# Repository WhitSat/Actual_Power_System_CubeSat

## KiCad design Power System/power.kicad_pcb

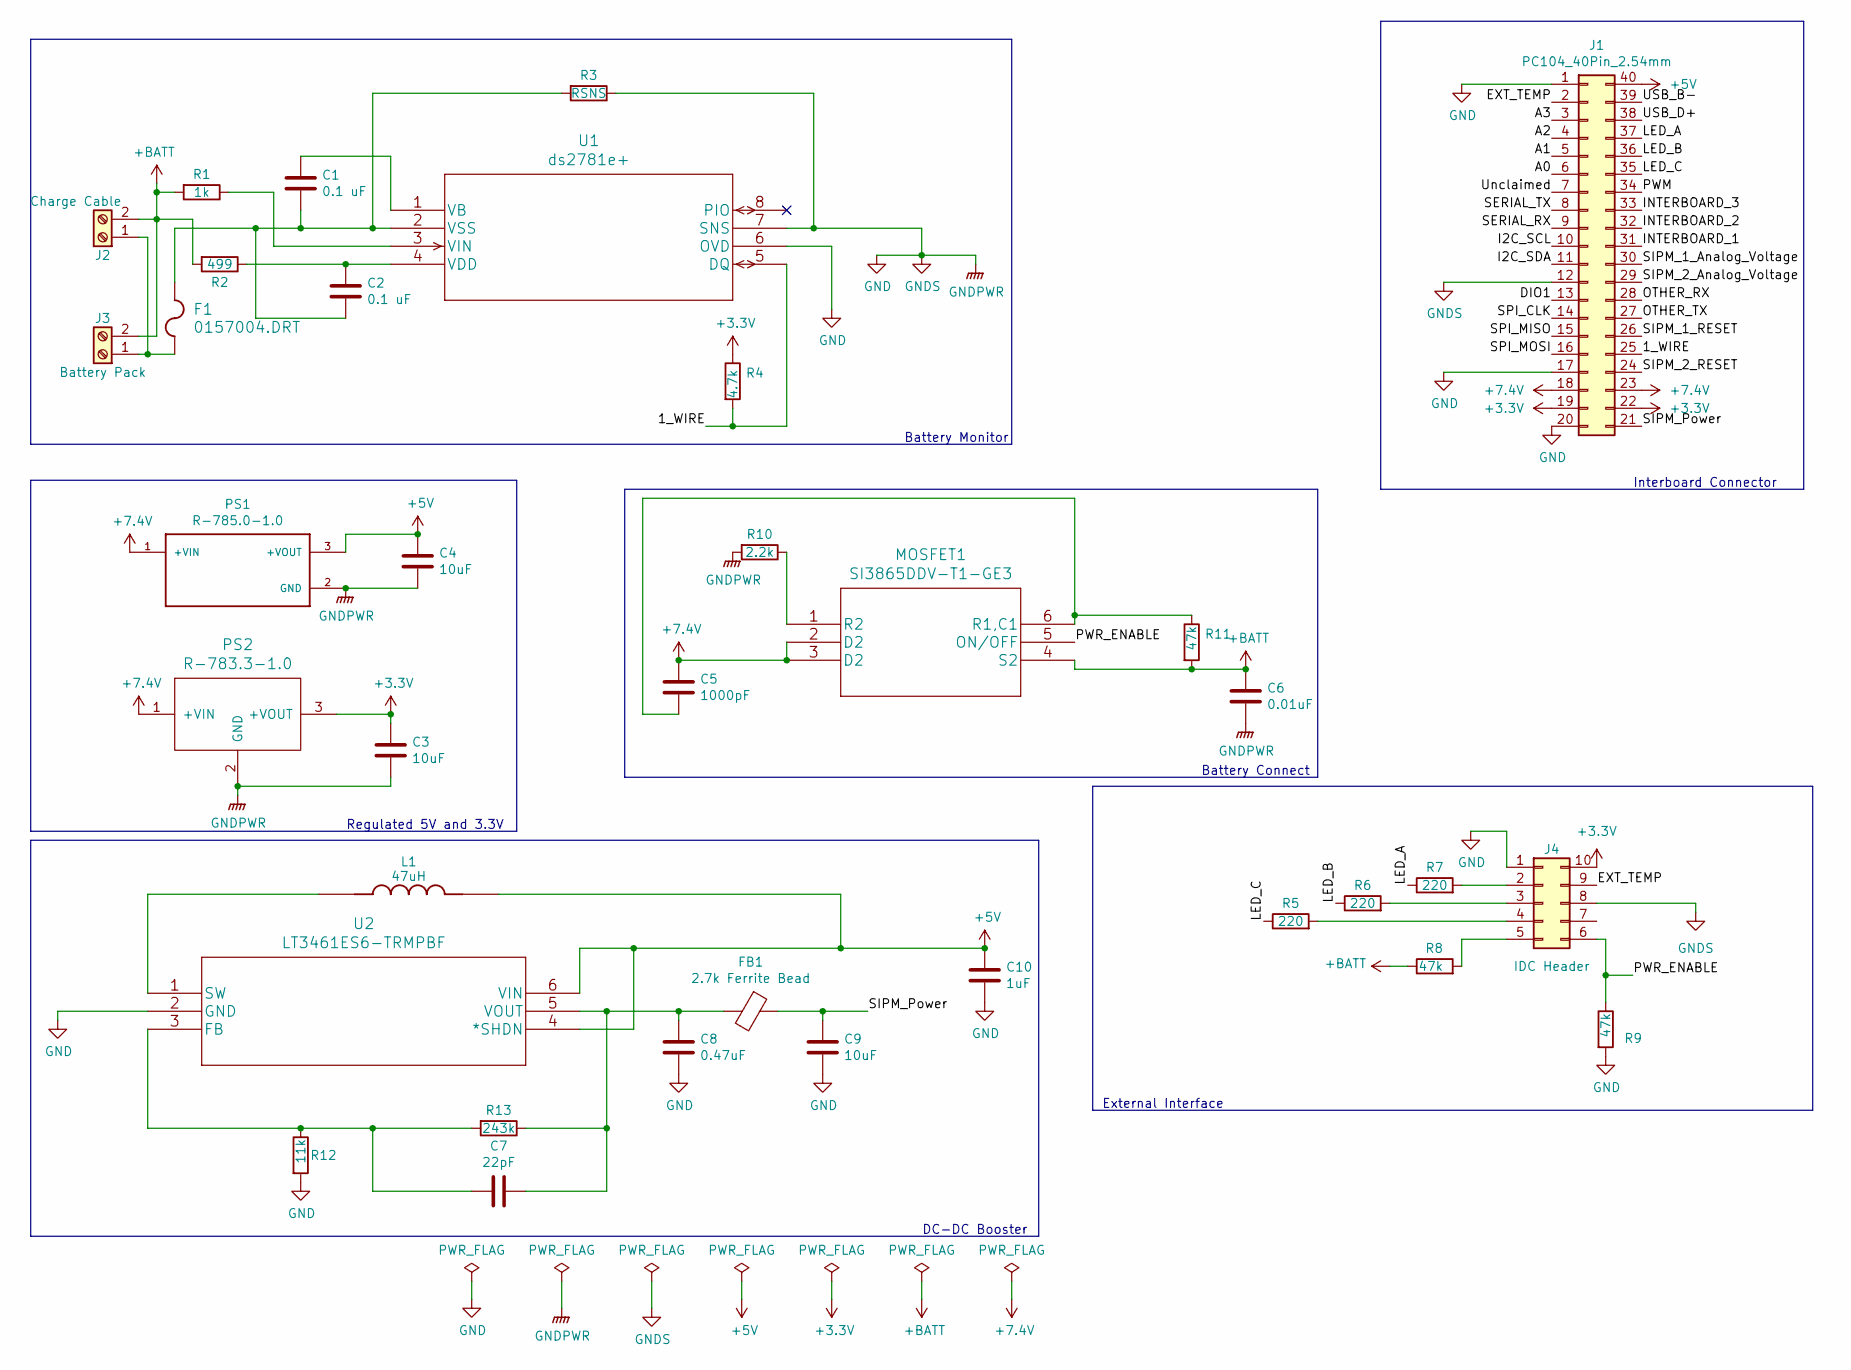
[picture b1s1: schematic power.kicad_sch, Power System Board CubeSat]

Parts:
C1, C2: 0.1 uF; C_1206_3216Metric_Pad1.33x1.80mm_HandSolder
C3, C4, C9: 10uF; C_1206_3216Metric_Pad1.33x1.80mm_HandSolder
C5: 1000pF; C_1206_3216Metric_Pad1.33x1.80mm_HandSolder
C6: 0.01uF; C_1206_3216Metric_Pad1.33x1.80mm_HandSolder
C7: 22pF; C_1206_3216Metric_Pad1.33x1.80mm_HandSolder
C8: 0.47uF; C_1206_3216Metric_Pad1.33x1.80mm_HandSolder
C10: 1uF; C_1206_3216Metric_Pad1.33x1.80mm_HandSolder
F1: 0157004.DRT; LittleFuse_0157004.DRT
FB1: 2.7k Ferrite Bead; BEADC2012X110N
J1: PC104_40Pin_2.54mm; PC104_40PinSocket_2.54mm
J2: Charge Cable; TerminalBlock_4Ucon_1x02_P3.50mm_Horizontal
J3: Battery Pack; TerminalBlock_4Ucon_1x02_P3.50mm_Horizontal
J4: IDC Header; IDC-Header_2x05_P2.54mm_Vertical
L1: 47uH; IND_LQH43NH470J03L; PARTREV N/A
MOSFET1: SI3865DDV-T1-GE3
PS1: R-785.0-1.0; RECOM-R-78xx-1.0
PS2: R-783.3-1.0; RECOM-R-78xx-1.0
R1: 1k; R_1206_3216Metric_Pad1.30x1.75mm_HandSolder
R2: 499; R_1206_3216Metric_Pad1.30x1.75mm_HandSolder
R3: RSNS; R_2010_5025Metric_Pad1.40x2.65mm_HandSolder
R4: 4.7k; R_1206_3216Metric_Pad1.30x1.75mm_HandSolder
R5, R6, R7: 220; R_1206_3216Metric_Pad1.30x1.75mm_HandSolder
R8, R9, R11: 47k; R_1206_3216Metric_Pad1.30x1.75mm_HandSolder
R10: 2.2k; R_1206_3216Metric_Pad1.30x1.75mm_HandSolder
R12: 11k; R_1206_3216Metric_Pad1.30x1.75mm_HandSolder
R13: 243k; R_1206_3216Metric_Pad1.30x1.75mm_HandSolder
U1: ds2781e+; ds2781e&plus_
U2: LT3461ES6-TRMPBF

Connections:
+3V3: C3.1, J1.19, J1.22, J4.10, PS2.3 (+VOUT), R4.1
+5V: C4.1, C10.1, J1.40, L1.2, PS1.3 (+VOUT), U2.4 (*SHDN), U2.6 (VIN)
+7.4V: C5.1, J1.18, J1.23, MOSFET1.2 (D2), MOSFET1.3 (D2), PS1.1 (+VIN), PS2.1 (+VIN)
+BATT: C6.1, J2.2, J3.2, MOSFET1.4 (S2), R1.2, R2.2, R8.1, R11.2
/1_WIRE: J1.25, R4.2, U1.5 (DQ)
/A0: J1.6
/A1: J1.5
/A2: J1.4
/A3: J1.3
/DIO1: J1.13
/EXT_TEMP: J1.2, J4.9
/I2C_SCL: J1.10
/I2C_SDA: J1.11
/INTERBOARD_1: J1.31
/INTERBOARD_2: J1.32
/INTERBOARD_3: J1.33
/LED_A: J1.37, R7.1
/LED_B: J1.36, R6.1
/LED_C: J1.35, R5.1
/OTHER_RX: J1.28
/OTHER_TX: J1.27
/PWM: J1.34
/PWR_ENABLE: J4.6, MOSFET1.5 (ON/OFF), R9.1
/SERIAL_RX: J1.9
/SERIAL_TX: J1.8
/SIPM_1_Analog_Voltage: J1.30
/SIPM_1_RESET: J1.26
/SIPM_2_Analog_Voltage: J1.29
/SIPM_2_RESET: J1.24
/SIPM_Power: C9.1, FB1.1, J1.21
/SPI_CLK: J1.14
/SPI_MISO: J1.15
/SPI_MOSI: J1.16
/USB_B-: J1.39
/USB_D+: J1.38
/Unclaimed: J1.7
GND: C3.2, C4.2, C6.2, C8.2, C9.2, C10.2, J1.1, J1.12, J1.17, J1.20, J4.1, J4.8, PS1.2 (GND), PS2.2 (GND), R3.1, R9.2, R10.2, R12.2, U1.6 (OVD), U1.7 (SNS), U2.2 (GND)
unnamed: C1.1, U1.1 (VB)
unnamed: C1.2, C2.2, F1.2, R3.2, U1.2 (VSS)
unnamed: C2.1, R2.1, U1.4 (VDD)
unnamed: C5.2, MOSFET1.6 (R1,C1), R11.1
unnamed: C7.1, C8.1, FB1.2, R13.1, U2.5 (VOUT)
unnamed: C7.2, R12.1, R13.2, U2.3 (FB)
unnamed: F1.1, J2.1, J3.1
unnamed: L1.1, U2.1 (SW)
unnamed: MOSFET1.1 (R2), R10.1
unnamed: R1.1, U1.3 (VIN)
unnamed: J4.4, R5.2
unnamed: J4.3, R6.2
unnamed: J4.2, R7.2
unnamed: J4.5, R8.2

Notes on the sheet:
Interboard Connector
Battery Monitor
External Interface
DC-DC Booster
Regulated 5V and 3.3V
Battery Connect

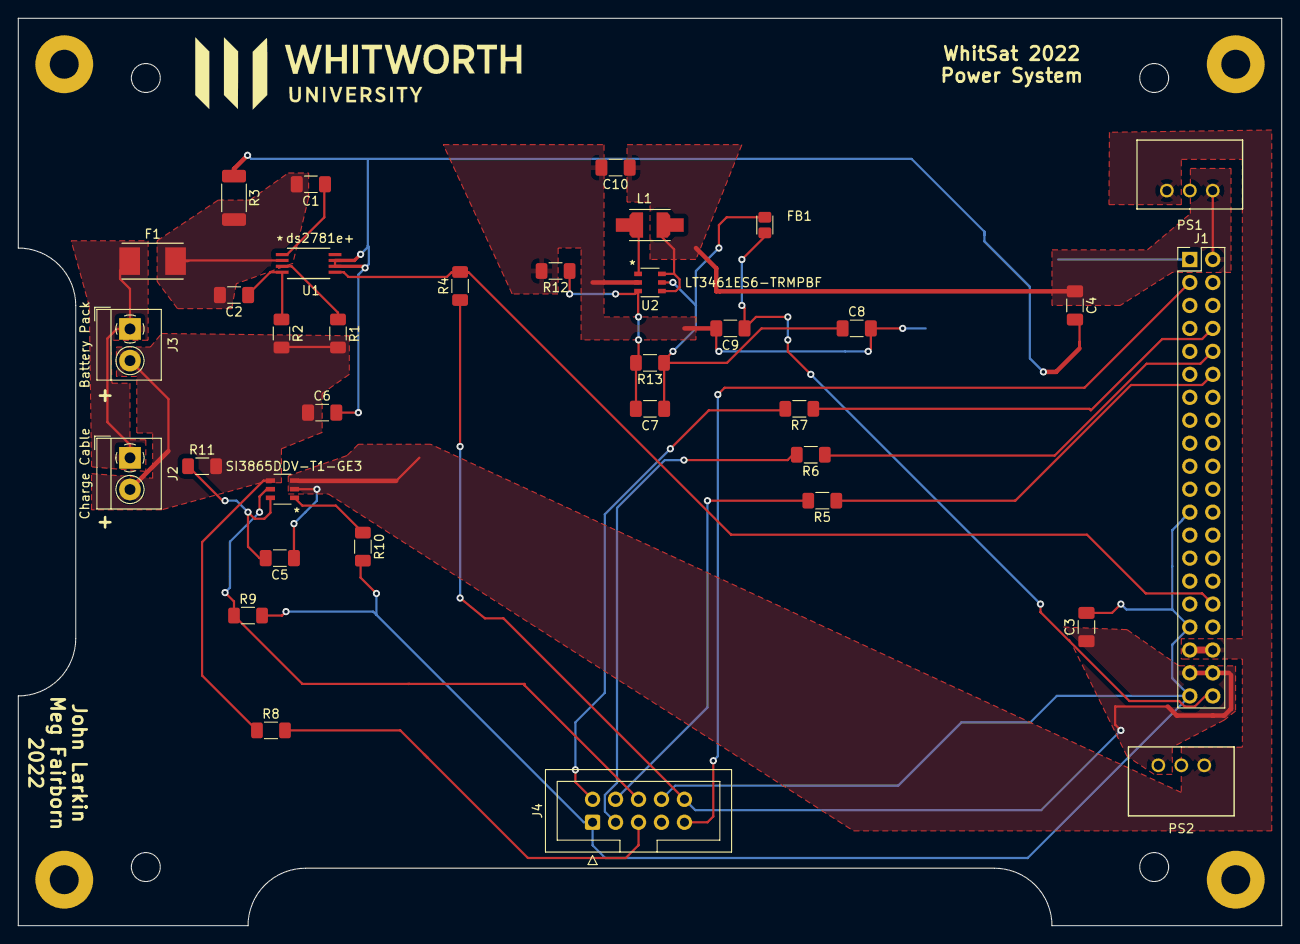
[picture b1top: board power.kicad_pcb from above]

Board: 2 copper layers, 139.7 x 100.3 mm, 35 parts (0 on the bottom side), 26 nets.

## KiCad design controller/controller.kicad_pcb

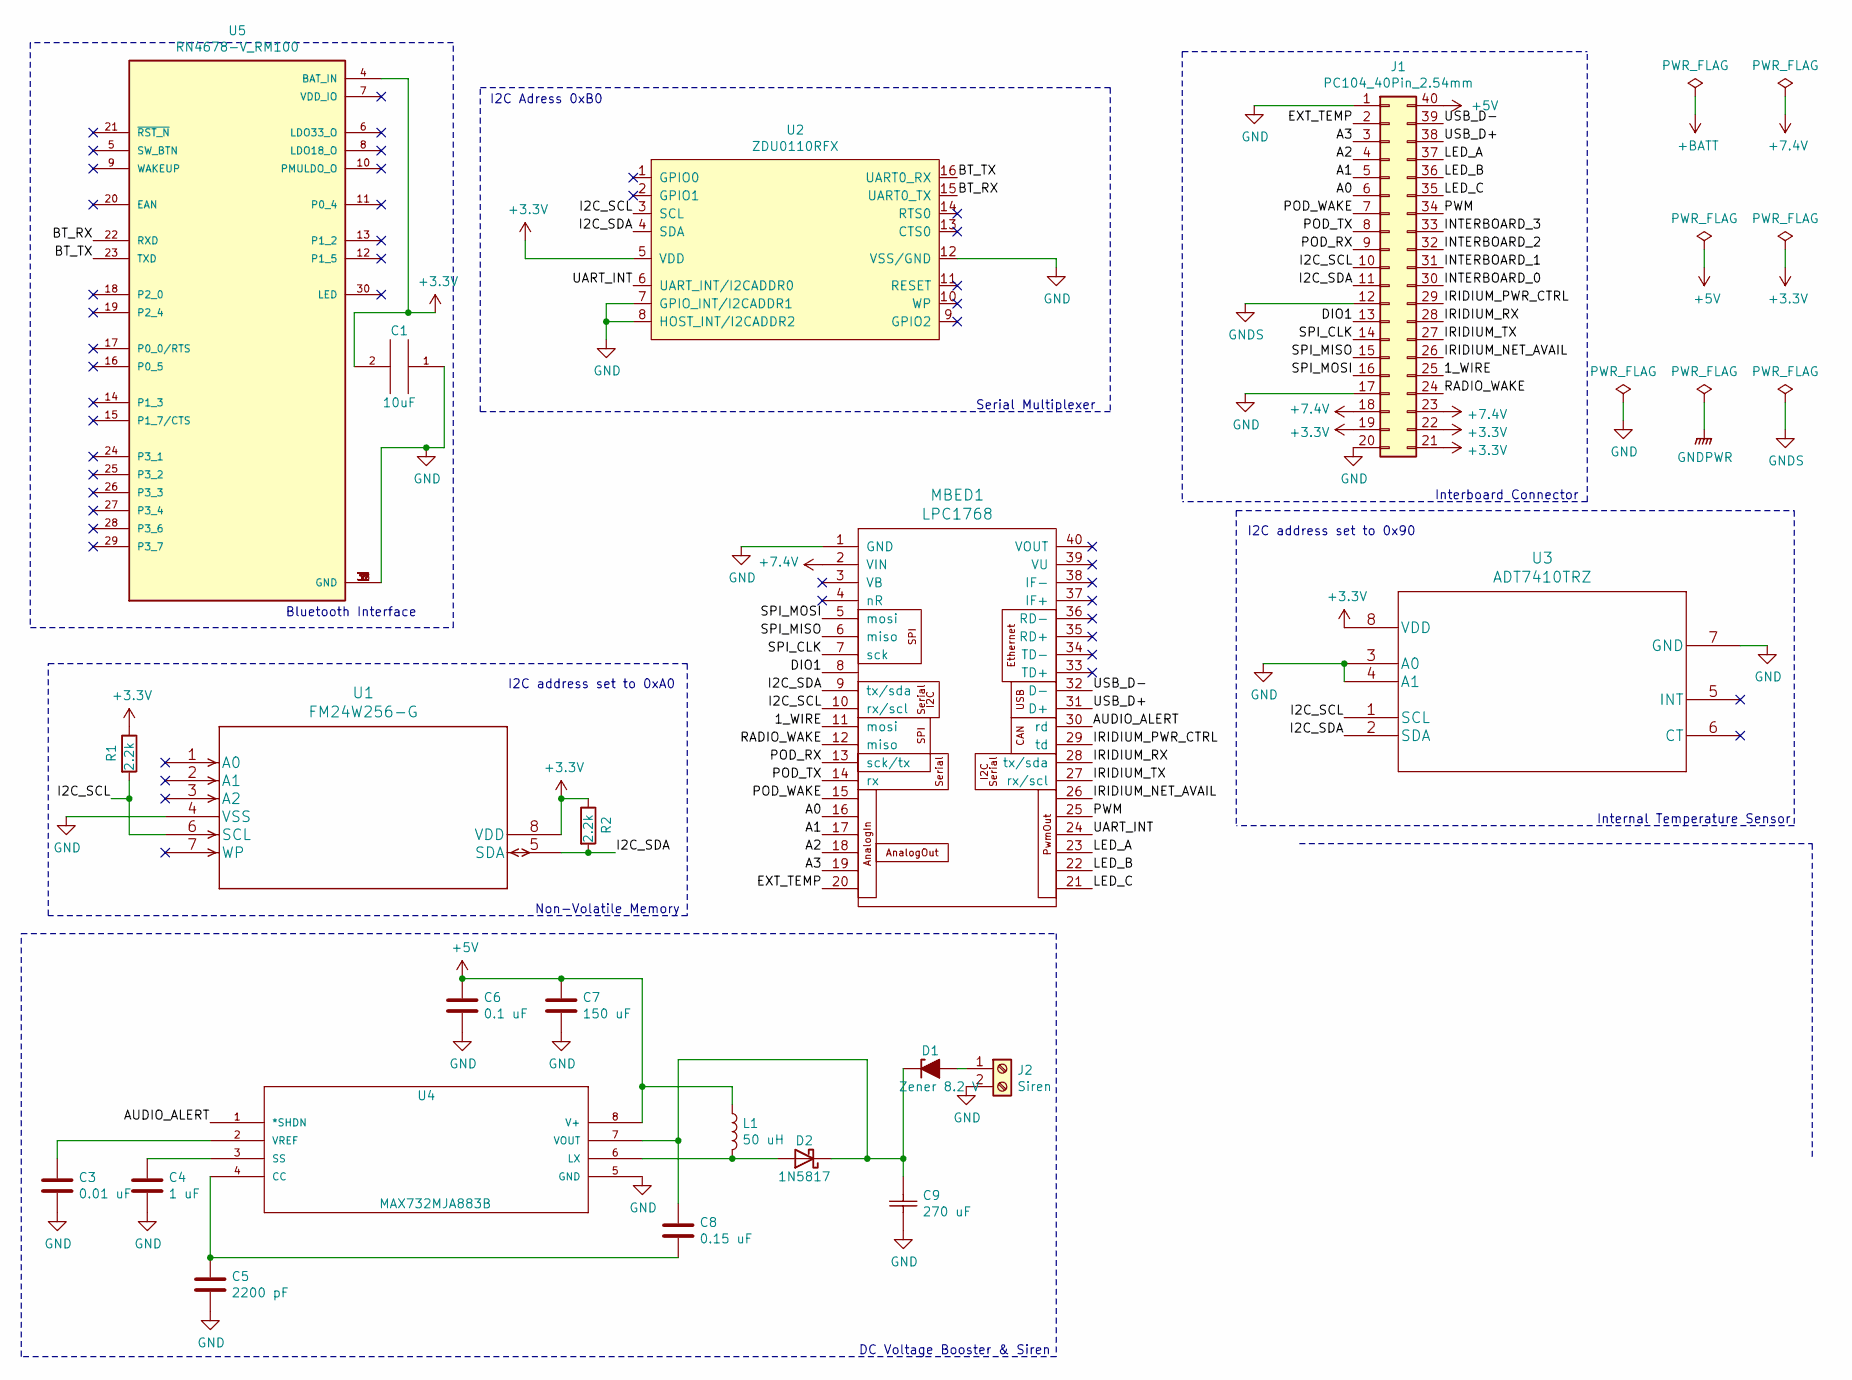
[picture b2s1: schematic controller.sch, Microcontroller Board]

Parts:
C1: 10uF; 1206
C3: 0.01 uF; C_1206_3216Metric_Pad1.42x1.75mm_HandSolder
C4: 1 uF; C_1206_3216Metric_Pad1.42x1.75mm_HandSolder
C5: 2200 pF; C_1206_3216Metric_Pad1.42x1.75mm_HandSolder
C6: 0.1 uF; C_1206_3216Metric_Pad1.42x1.75mm_HandSolder
C7: 150 uF; C_1206_3216Metric_Pad1.42x1.75mm_HandSolder
C8: 0.15 uF; C_1206_3216Metric_Pad1.42x1.75mm_HandSolder
C9: 270 uF; PCV1E271MCL2GS
D1: Zener 8.2 V; D_DO-41_SOD81_P10.16mm_Horizontal
D2: 1N5817; D_DO-41_SOD81_P10.16mm_Horizontal
J1: PC104_40Pin_2.54mm; PC104_40PinSocket_2.54mm
J2: Siren; TerminalBlock_4Ucon_1x02_P3.50mm_Vertical
L1: 50 uH; L_Wuerth_WE-PD-Typ-LS_Handsoldering
MBED1: LPC1768; mbed-lpc1768
R1, R2: 2.2k; R_1206_3216Metric_Pad1.42x1.75mm_HandSolder
U1: FM24W256-G
U2: ZDU0110RFX
U3: ADT7410TRZ
U4: MAX732MJA883B; 21-0045A_8
U5: RN4678-V_RM100; RM100

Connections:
+3V3: C1.2, J1.19, J1.21, J1.22, R1.1, R2.1, U1.8 (VDD), U2.5 (VDD), U3.8 (VDD), U5.4 (BAT_IN)
+5V: C6.1, C7.1, J1.40, L1.1, U4.8 (V+)
+7.4V: J1.18, J1.23, MBED1.2 (VIN)
/1_WIRE: J1.25, MBED1.11 (mosi)
/A0: J1.6, MBED1.16
/A1: J1.5, MBED1.17
/A2: J1.4, MBED1.18
/A3: J1.3, MBED1.19
/AUDIO_ALERT: MBED1.30 (rd), U4.1 (*SHDN)
/BT_RX: U2.15 (UART0_TX), U5.22 (RXD)
/BT_TX: U2.16 (UART0_RX), U5.23 (TXD)
/DIO1: J1.13, MBED1.8
/EXT_TEMP: J1.2, MBED1.20
/I2C_SCL: J1.10, MBED1.10 (rx/scl), R1.2, U1.6 (SCL), U2.3 (SCL), U3.1 (SCL)
/I2C_SDA: J1.11, MBED1.9 (tx/sda), R2.2, U1.5 (SDA), U2.4 (SDA), U3.2 (SDA)
/INTERBOARD_0: J1.30
/INTERBOARD_1: J1.31
/INTERBOARD_2: J1.32
/INTERBOARD_3: J1.33
/IRIDIUM_NET_AVAIL: J1.26, MBED1.26
/IRIDIUM_PWR_CTRL: J1.29, MBED1.29 (td)
/IRIDIUM_RX: J1.28, MBED1.28 (tx/sda)
/IRIDIUM_TX: J1.27, MBED1.27 (rx/scl)
/LED_A: J1.37, MBED1.23
/LED_B: J1.36, MBED1.22
/LED_C: J1.35, MBED1.21
/POD_RX: J1.9, MBED1.13 (sck/tx)
/POD_TX: J1.8, MBED1.14 (rx)
/POD_WAKE: J1.7, MBED1.15
/PWM: J1.34, MBED1.25
/RADIO_WAKE: J1.24, MBED1.12 (miso)
/SPI_CLK: J1.14, MBED1.7 (sck)
/SPI_MISO: J1.15, MBED1.6 (miso)
/SPI_MOSI: J1.16, MBED1.5 (mosi)
/UART_INT: MBED1.24, U2.6 (UART_INT/I2CADDR0)
/USB_D+: J1.38, MBED1.31 (D+)
/USB_D-: J1.39, MBED1.32 (D-)
GND: C1.1, C3.2, C4.2, C5.2, C6.2, C7.2, C9.2, J1.1, J1.17, J1.20, J2.2, MBED1.1 (GND), U1.4 (VSS), U2.7 (GPIO_INT/I2CADDR1), U2.8 (HOST_INT/I2CADDR2), U2.12 (VSS/GND), U3.3 (A0), U3.4 (A1), U3.7 (GND), U4.5 (GND), U5.1 (GND), U5.2 (GND), U5.3 (GND), U5.31 (GND), U5.32 (GND), U5.33 (GND)
GNDS: J1.12
unnamed: C3.1, U4.2 (VREF)
unnamed: C4.1, U4.3 (SS)
unnamed: C5.1, C8.2, U4.4 (CC)
unnamed: C8.1, C9.1, D1.1 (K), D2.1 (K), U4.7 (VOUT)
unnamed: D1.2 (A), J2.1
unnamed: D2.2 (A), L1.2, U4.6 (LX)

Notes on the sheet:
I2C address set to 0x90
Interboard Connector
Internal Temperature Sensor
Non-Volatile Memory
I2C address set to 0xA0
Bluetooth Interface
DC Voltage Booster & Siren
Serial Multiplexer
I2C Adress 0xB0

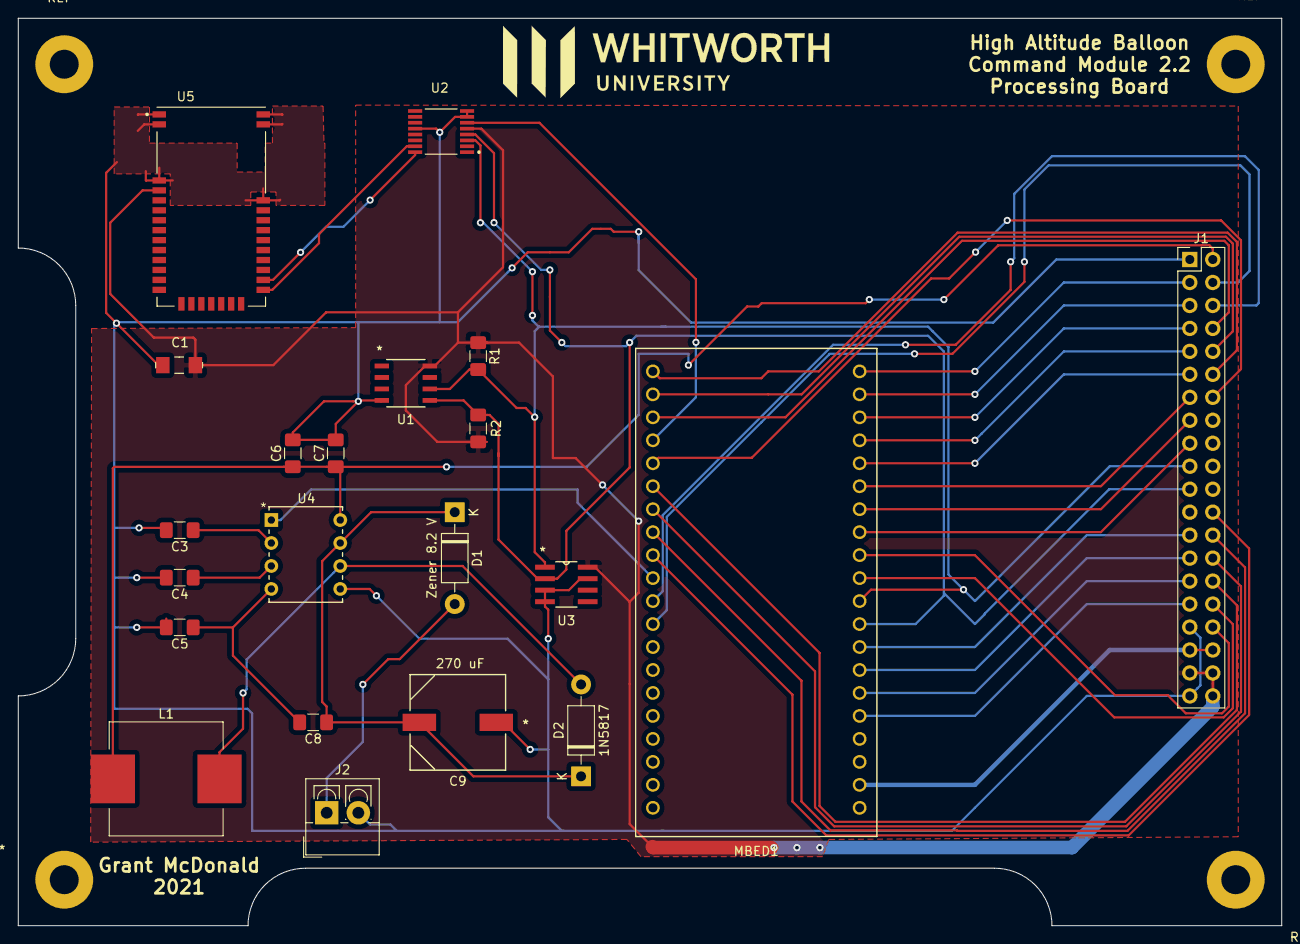
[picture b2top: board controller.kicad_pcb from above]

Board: 2 copper layers, 139.7 x 100.3 mm, 21 parts (0 on the bottom side), 40 nets.

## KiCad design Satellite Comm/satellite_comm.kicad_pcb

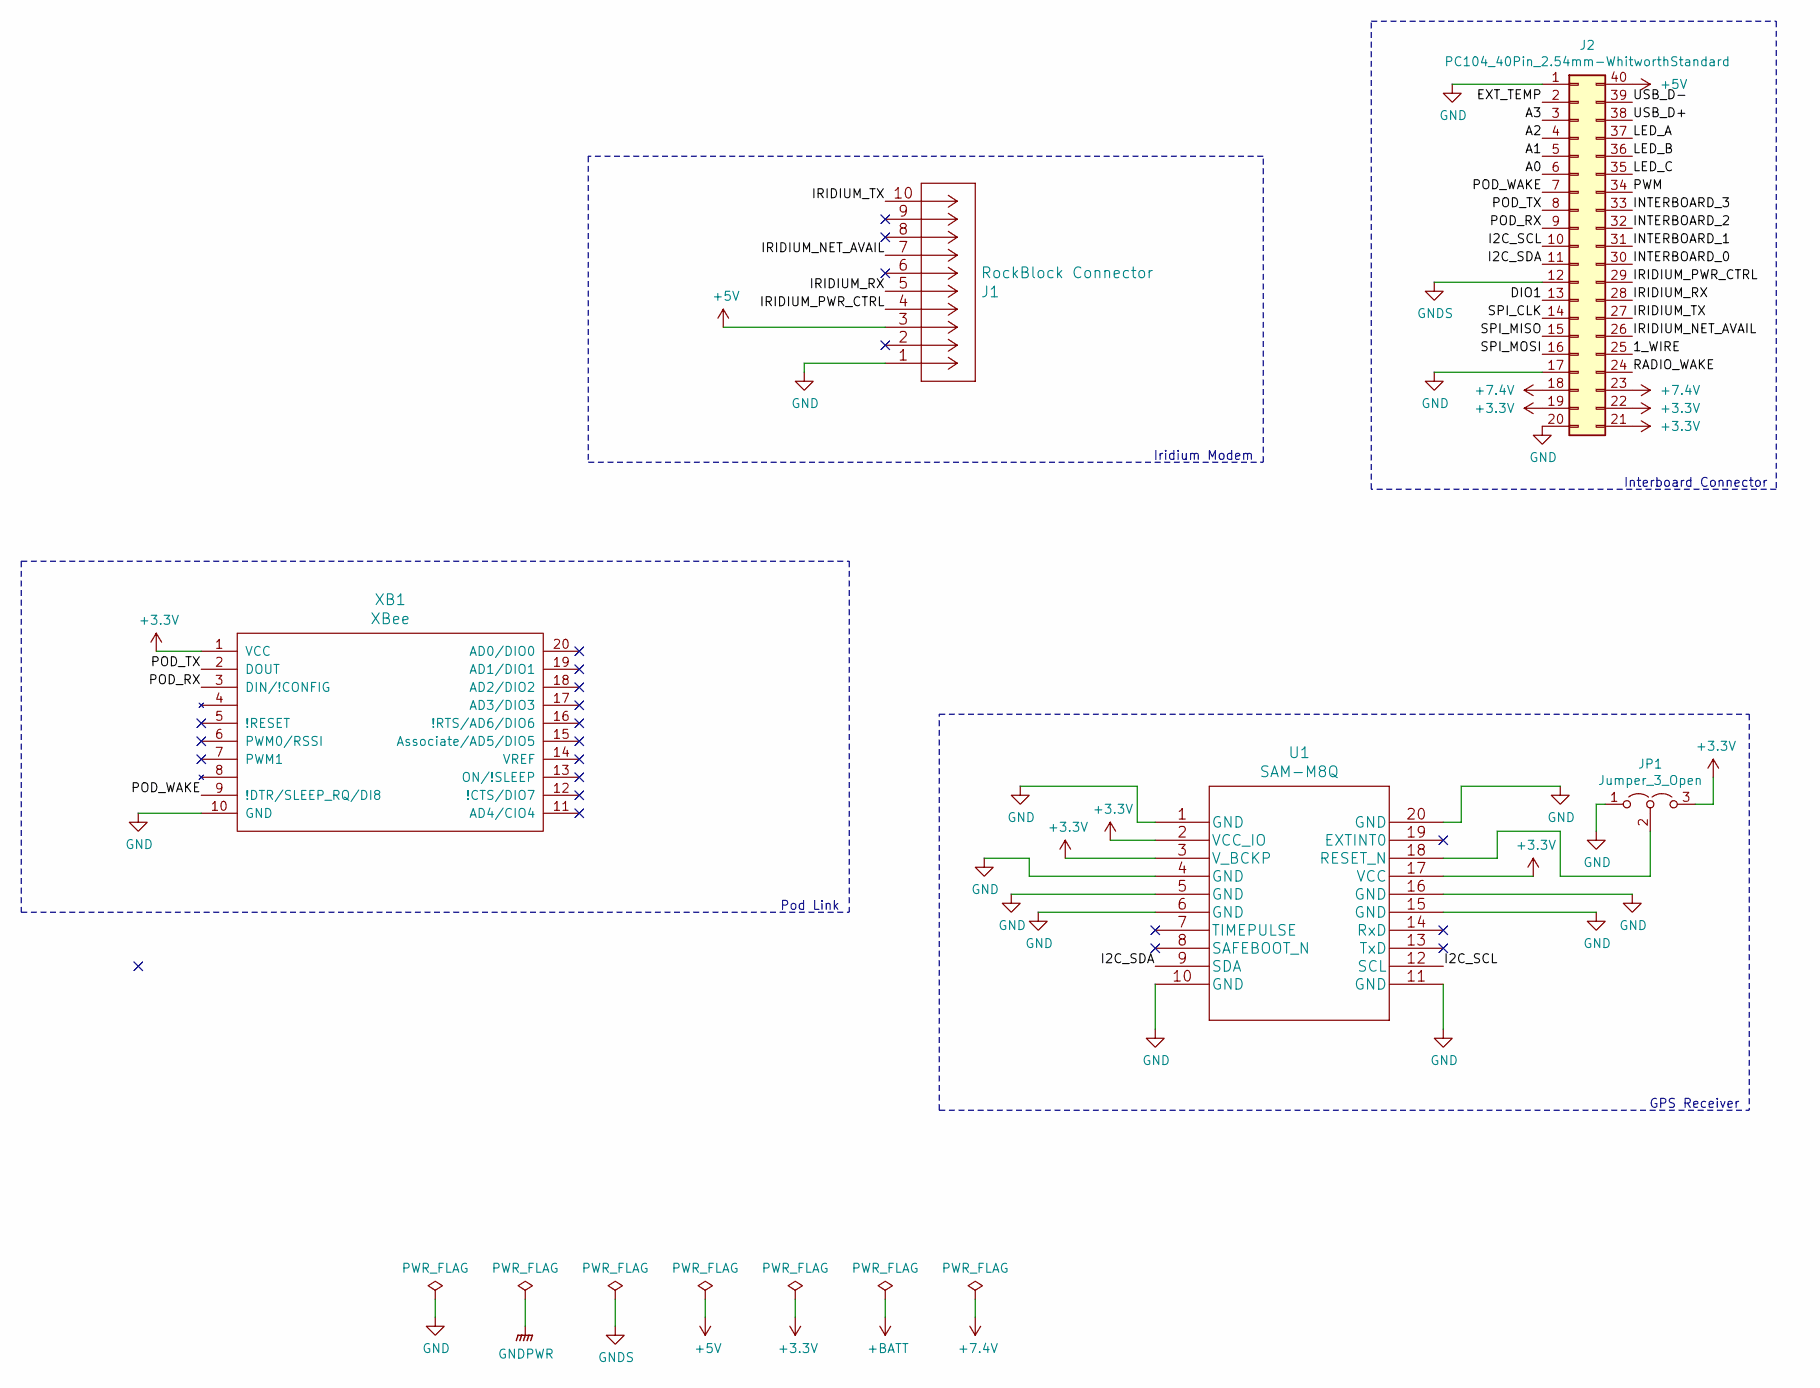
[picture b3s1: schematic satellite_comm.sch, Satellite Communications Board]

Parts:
J1: RockBlock Connector; Molex_PicoBlade_53398-1071_1x10-1MP_P1.25mm_Vertical
J2: PC104_40Pin_2.54mm-WhitworthStandard; PC104_40PinSocket_2.54mm
JP1: Jumper_3_Open; PinHeader_1x03_P2.54mm_Vertical
U1: SAM-M8Q; ublox_SAM-M8Q_HandSolder
XB1: XBee; xbee-standard

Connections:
+3V3: J2.19, J2.21, J2.22, JP1.3 (B), U1.2 (VCC_IO), U1.3 (V_BCKP), U1.17 (VCC), XB1.1 (VCC)
+5V: J1.3, J2.40
+7.4V: J2.18, J2.23
/1_WIRE: J2.25
/A0: J2.6
/A1: J2.5
/A2: J2.4
/A3: J2.3
/DIO1: J2.13
/EXT_TEMP: J2.2
/I2C_SCL: J2.10, U1.12 (SCL)
/I2C_SDA: J2.11, U1.9 (SDA)
/INTERBOARD_0: J2.30
/INTERBOARD_1: J2.31
/INTERBOARD_2: J2.32
/INTERBOARD_3: J2.33
/IRIDIUM_NET_AVAIL: J1.7, J2.26
/IRIDIUM_PWR_CTRL: J1.4, J2.29
/IRIDIUM_RX: J1.5, J2.28
/IRIDIUM_TX: J1.10, J2.27
/LED_A: J2.37
/LED_B: J2.36
/LED_C: J2.35
/POD_RX: J2.9, XB1.3 (DIN/!CONFIG)
/POD_TX: J2.8, XB1.2 (DOUT)
/POD_WAKE: J2.7, XB1.9 (!DTR/SLEEP_RQ/DI8)
/PWM: J2.34
/RADIO_WAKE: J2.24
/SPI_CLK: J2.14
/SPI_MISO: J2.15
/SPI_MOSI: J2.16
/USB_D+: J2.38
/USB_D-: J2.39
GND: J1.1, J2.1, J2.17, J2.20, JP1.1 (A), U1.1 (GND), U1.4 (GND), U1.5 (GND), U1.6 (GND), U1.10 (GND), U1.11 (GND), U1.15 (GND), U1.16 (GND), U1.20 (GND), XB1.10 (GND)
GNDS: J2.12
unnamed: JP1.2 (C), U1.18 (RESET_N)

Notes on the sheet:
Interboard Connector
Iridium Modem
GPS Receiver
Pod Link

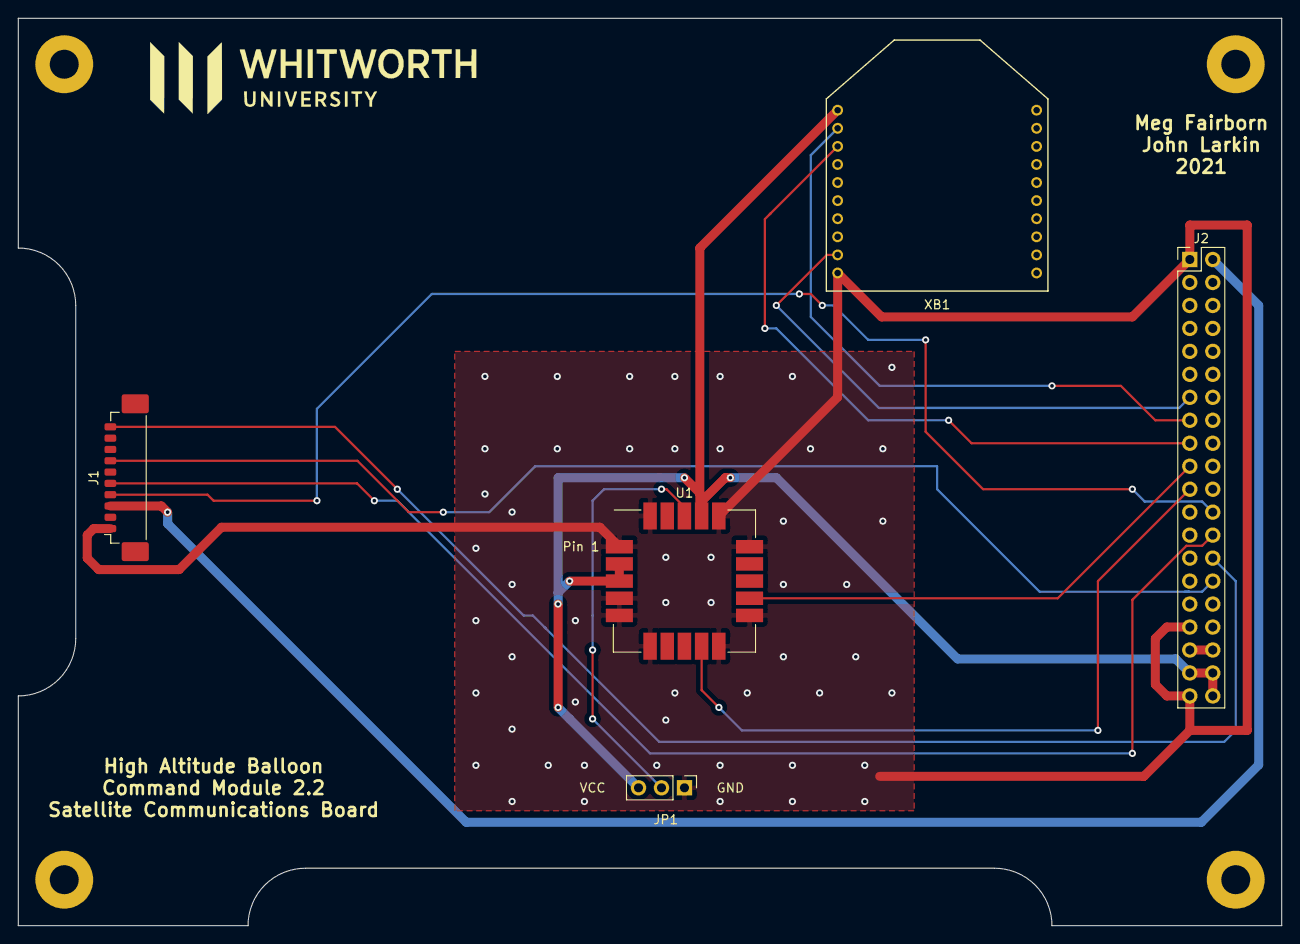
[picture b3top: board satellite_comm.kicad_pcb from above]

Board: 2 copper layers, 139.7 x 100.3 mm, 5 parts (0 on the bottom side), 14 nets.

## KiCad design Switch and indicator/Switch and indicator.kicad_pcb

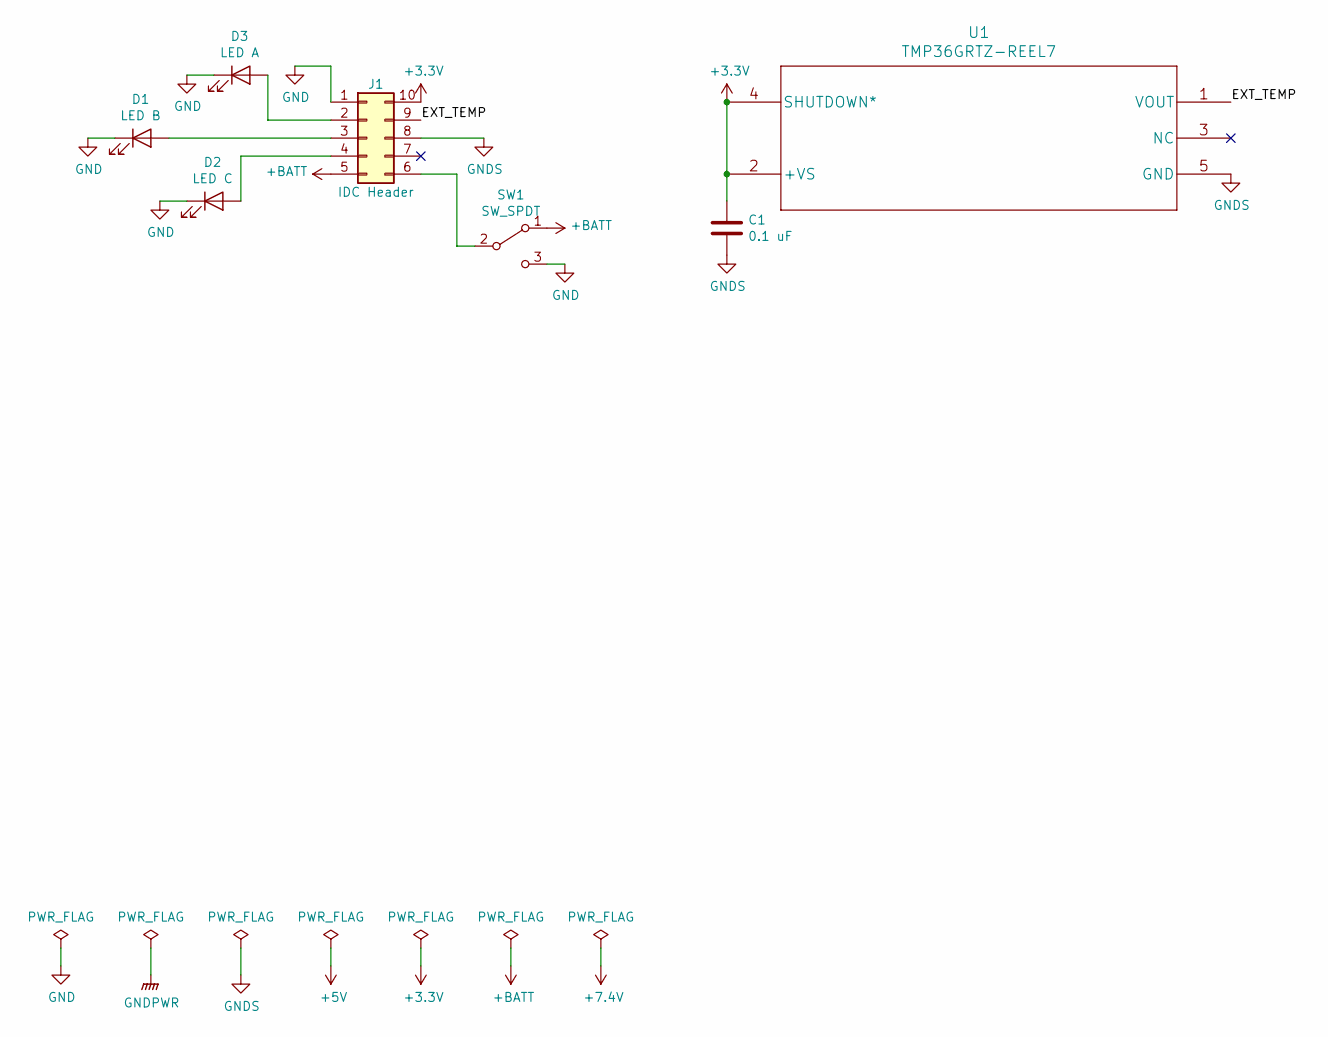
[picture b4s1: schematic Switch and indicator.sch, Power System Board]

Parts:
C1: 0.1 uF; C_1206_3216Metric_Pad1.42x1.75mm_HandSolder
D1: LED B; LED_1206_3216Metric_Pad1.42x1.75mm_HandSolder
D2: LED C; LED_1206_3216Metric_Pad1.42x1.75mm_HandSolder
D3: LED A; LED_1206_3216Metric_Pad1.42x1.75mm_HandSolder
J1: IDC Header; 61201020621
SW1: SW_SPDT; JS102011SCQN
U1: TMP36GRTZ-REEL7; TMP36GRTZ-SOT23

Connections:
+3V3: C1.1, J1.10, U1.2 (+VS), U1.4 (SHUTDOWN*)
+BATT: J1.5, SW1.1 (A)
/EXT_TEMP: J1.9, U1.1 (VOUT)
GND: D1.1 (K), D2.1 (K), D3.1 (K), J1.1, SW1.3 (C)
GNDS: C1.2, J1.8, U1.5 (GND)
unnamed: D1.2 (A), J1.3
unnamed: D2.2 (A), J1.4
unnamed: D3.2 (A), J1.2
unnamed: J1.6, SW1.2 (B)

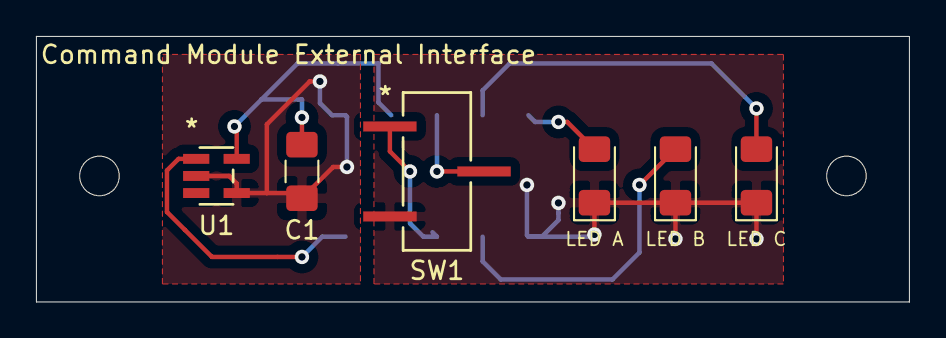
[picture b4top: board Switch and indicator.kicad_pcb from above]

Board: 2 copper layers, 48.5 x 14.8 mm, 7 parts (1 on the bottom side), 9 nets.

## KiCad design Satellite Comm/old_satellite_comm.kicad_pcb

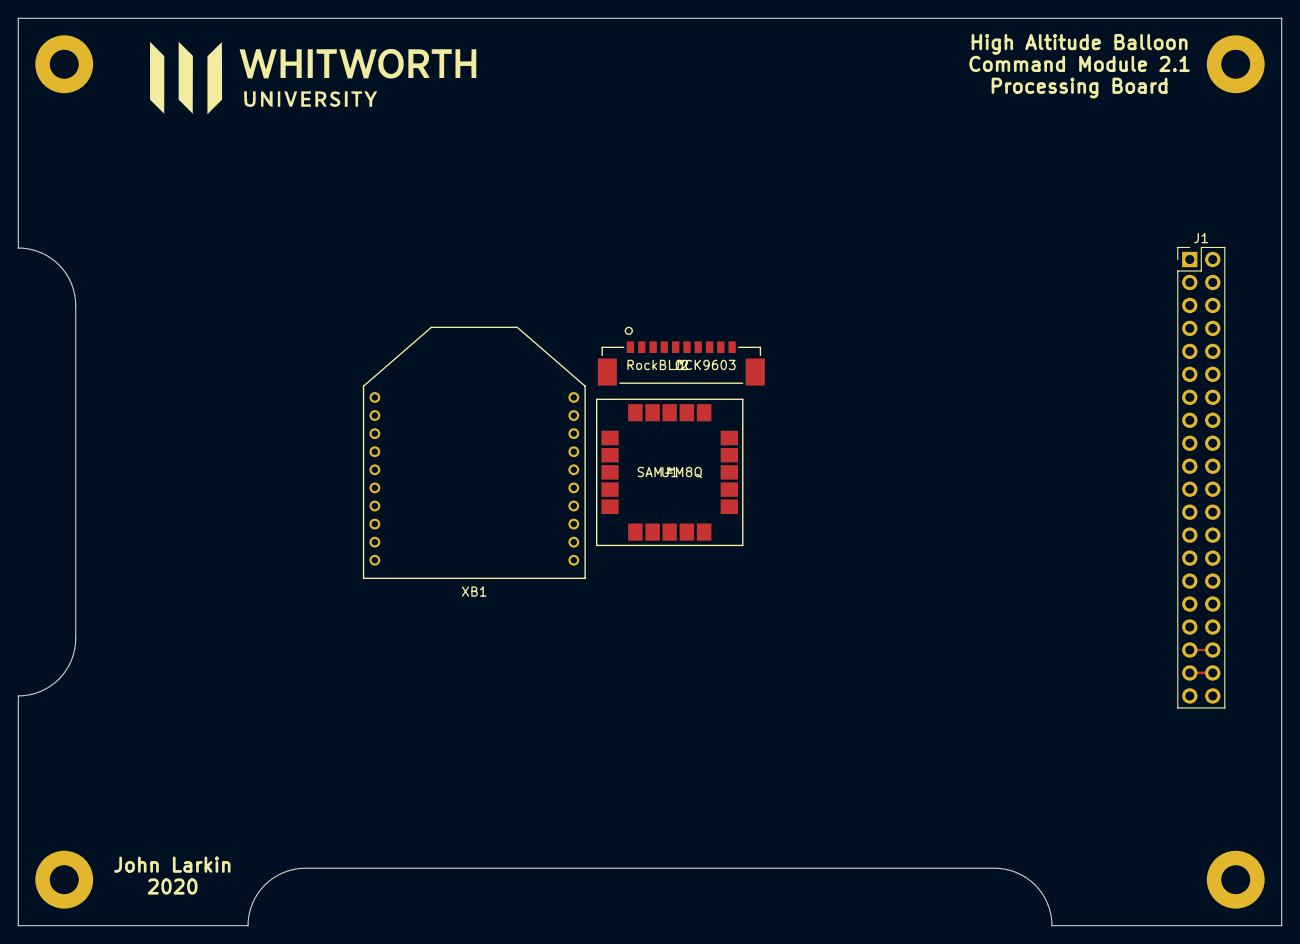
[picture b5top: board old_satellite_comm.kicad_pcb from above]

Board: 2 copper layers, 139.7 x 100.3 mm, 4 parts (0 on the bottom side), 8 nets.

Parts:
J1: PC104_40Pin_2.54mm; PC104_40PinSocket_2.54mm
J2: RockBLOCK9603; Molex_53398-1071
U1: SAM-M8Q
XB1: XBee; xbee-standard

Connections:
+3V3: J1.19, J1.21, J1.22
+5V: J1.40, J2.8
+7.4V: J1.18, J1.23
/IRIDIUM_NET_AVAIL: J1.26, J2.4
/IRIDIUM_PWR_CTRL: J1.29, J2.7
/IRIDIUM_RX: J1.28, J2.6
/IRIDIUM_TX: J1.27, J2.1
GND: J1.1, J1.17, J1.20, J2.10

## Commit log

2021-07-12 Controller updated
2021-07-12 Add "WhitworthStandard" library of parts
2021-07-14 Add Wuerth Electronik Bluetooth module
    Also modified location of Whitworth standard library of parts
2021-07-14 First commit: Proteus III PCB footprint
2021-07-16 Update footprints and symbols for power
2021-07-16 Updated controller board with proteus III and Zilog multiplexer
2021-07-16 2nd commit mounting through holes added
2021-07-16 ZDU0110RFX I2C address set
2021-07-20 Added SI3865DDVT1GE3 symbol
2021-07-22 Added new zones on schematic diagram
2021-07-22 Got rid of short and changed some notation
2021-07-22 deleted old regulator and battery connect from schematic
2021-07-22 generated a netlist
2021-07-23 Made some changes, likely to component list.
2021-07-23 Updated PCB & fixed schematic
2021-07-23 Resized a couple fill zones...
2021-07-23 Further resized fill zones...
2021-07-26 Pretty sure power system fill zones are done
    I don't know why it wants to commit changes to the schematic?
2021-07-27 moved components away from each other
2021-07-27 moved C6 a little more and changed track layout a little
2021-07-28 Improve 3.3 V fill zone
2021-07-30 Fill zone rework
2021-07-30 Edited values of resistors on schematic
2021-07-30 Deleted all caches and renamed files...
2021-07-30 caches are still deleted added "rescues" back. Added Whitworth Standard library
2021-07-30 Add PC104 connector to Whitworth Standard symbol library
2021-08-02 Stared working on schematic, not all pins labeled or connected yet...
2021-08-02 most of the pins connected...
2021-08-02 added the jumper/finished pin connections
2021-08-02 corrected wrongly assigned pins
2021-08-02 fixed pin assignments
2021-08-02 generated netlists, assigned footprints, flipped connector to rockblock
2021-08-02 silks are not very clean, laid out components, added front ground plane
2021-08-04 started working on tracks
2021-08-04 made a couple more changes- switched out through board connector bc J1 had all pins wrong. placed j2 precisely over j1 and deleted j1
2021-08-04 routed all tracks... may want to move some of the ones coming from J1
2021-08-04 made all ground and power tracks thicker; decreased front copper trails through ground plane
2021-08-04 made the weird small trails thicker
2021-08-04 Made unimportant aesthetic changes...
2021-08-04 Added one more ground track
2021-08-04 minor, unimportant updates (deleting iridium_ri label since we aren't connecting that)
2021-08-09 Update satellite_comm.kicad_pcb
    Add bottom ground plane. Connect ground planes with via mesh.
2021-08-18 Controller board 2.2
2021-11-17 Added DC-DC Booster to schematic
2021-11-17 Attempting to assign footprints to the components...
2021-11-17 Tried routing things using recommendations. Late though- may be unideal...
2021-11-17 Changed text on board to say WhitSat instead of High Altitude Balloon Command Module 2
2021-12-10 Renamed pins on through-board connector
2021-12-10 Swapped LT3461a for LT3461 and changed pins on connector
2021-12-10 Changed POD_TX and POD_RX to SERIAL_RX and SERIAL_TX
2021-12-11 Routed SIPM_Power and renamed Battery Voltage to unclaimed
2021-12-22 Switched some footprints and created gerber files
2022-05-04 Updated parts - hopefully commits properly
    Added the correct footprint for the ferrite bead and changed a couple parts' values.
2022-05-06 Fingers Crossed This Doesn't Mess Stuff Up
    GitHub lost track of the repository on my computers, and I messed a bunch of stuff up trying to fix the issue, but I think it is fixed now... I also added the old connector for the switch Dr. Larkin 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

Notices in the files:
parts and their libraries:
Copyright 2016 Accelerated Designs. All rights reserved.
Copyright 2021 Accelerated Designs. All rights reserved.
